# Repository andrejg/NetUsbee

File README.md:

# NetUsbee
A redraw of the famous network and usb adapter for 16/32bit Atari computers based on RTL8019AS and ISP1160

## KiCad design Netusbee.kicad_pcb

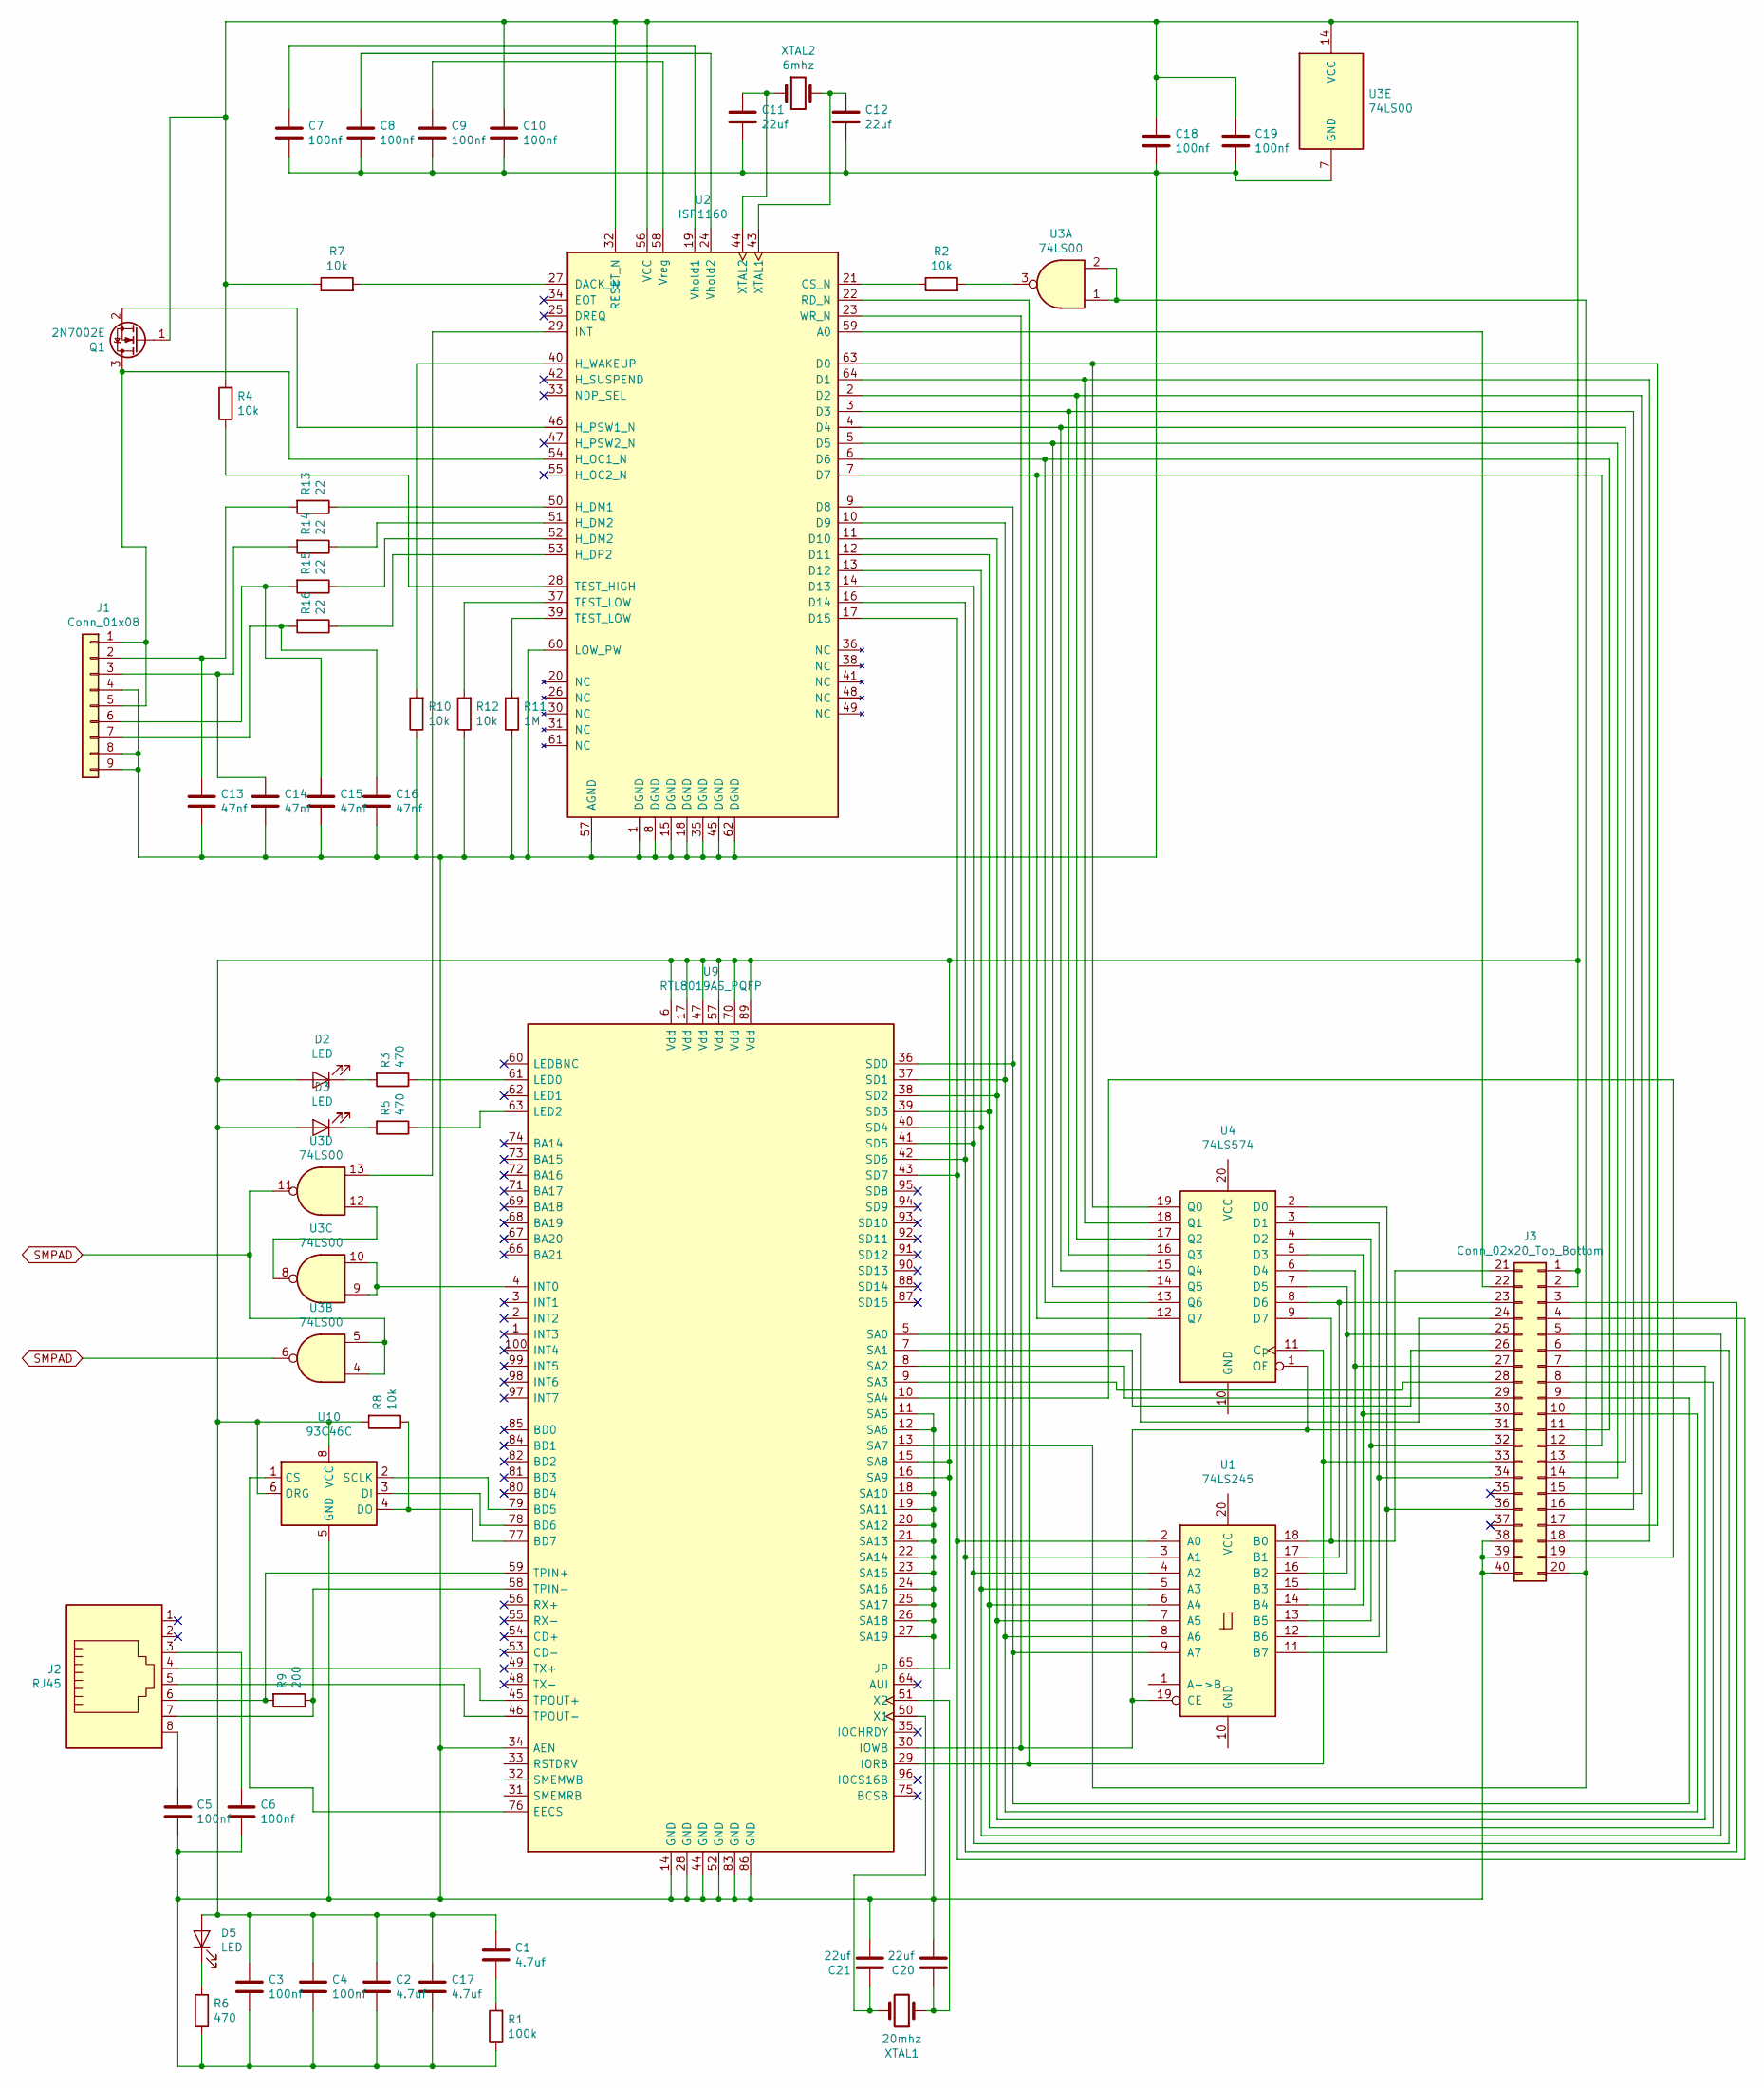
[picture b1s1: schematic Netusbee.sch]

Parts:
C1, C2, C17: 4.7uf; C_0805_2012Metric_Pad1.15x1.40mm_HandSolder
C3, C4, C5, C6, C7, C8, C9, C10, C18, C19: 100nf; C_0603_1608Metric_Pad1.05x0.95mm_HandSolder
C11, C12, C20, C21: 22uf; C_0603_1608Metric_Pad1.05x0.95mm_HandSolder
C13, C14, C15, C16: 47nf; C_0603_1608Metric_Pad1.05x0.95mm_HandSolder
D2, D3, D5: LED
J1: Conn_01x08; USB_A_Wuerth_61400826021_Horizontal_Stacked
J2: RJ45; RJ45_Amphenol_54602-x08_Horizontal
J3: Conn_02x20_Top_Bottom; AtariCartConnector
Q1: 2N7002E; SOT-23
R1: 100k; R_0603_1608Metric_Pad1.05x0.95mm_HandSolder
R2, R4, R7, R8, R10, R12: 10k; R_0603_1608Metric_Pad1.05x0.95mm_HandSolder
R3, R5, R6: 470; R_0603_1608Metric_Pad1.05x0.95mm_HandSolder
R9: 200; R_0603_1608Metric_Pad1.05x0.95mm_HandSolder
R11: 1M; R_0603_1608Metric_Pad1.05x0.95mm_HandSolder
R13, R14, R15, R16: 22; R_0603_1608Metric_Pad1.05x0.95mm_HandSolder
U1: 74LS245; SO-20_12.8x7.5mm_P1.27mm
U2: ISP1160; TQFP-64_10x10mm_P0.5mm
U3: 74LS00; TSSOP-14_4.4x5mm_P0.65mm
U4: 74LS574; SO-20_12.8x7.5mm_P1.27mm
U9: RTL8019AS_PQFP; PQFP-100_14x20mm_P0.65mm
U10: 93C46C; SOIC-8_3.9x4.9mm_P1.27mm
XTAL1: 20mhz; Crystal_SMD_HC49-SD
XTAL2: 6mhz; Crystal_SMD_HC49-SD

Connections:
unnamed: C1.1, C2.1, C3.1, C4.1, C10.1, C17.1, C18.1, C19.1, D2.2 (A), D3.2 (A), D5.2 (A), J3.1, J3.2, Q1.1 (G), R4.2, R7.1, R8.2, U2.32 (RESET_N), U2.56 (VCC), U3.14 (VCC), U9.6 (Vdd), U9.15 (SA8), U9.16 (SA9), U9.17 (Vdd), U9.47 (Vdd), U9.57 (Vdd), U9.65 (JP), U9.70 (Vdd), U9.89 (Vdd), U10.6 (ORG), U10.8 (VCC)
unnamed: C1.2, R1.2
unnamed: C5.1, J2.8
unnamed: C6.1, J2.3
unnamed: C7.1, U2.19 (Vhold1)
unnamed: C8.1, U2.24 (Vhold2)
unnamed: C9.1, U2.58 (Vreg)
unnamed: C2.2, C3.2, C4.2, C5.2, C6.2, C7.2, C8.2, C9.2, C10.2, C11.2, C12.2, C13.2, C14.2, C15.2, C16.2, C17.2, C18.2, C19.2, C20.2, C21.2, J1.4, J1.8, J1.9, J3.38, J3.39, J3.40, R1.1, R6.1, R10.1, R11.1, R12.1, U2.1 (DGND), U2.8 (DGND), U2.15 (DGND), U2.18 (DGND), U2.35 (DGND), U2.45 (DGND), U2.57 (AGND), U2.60 (LOW_PW), U2.62 (DGND), U3.7 (GND), U9.11 (SA5), U9.12 (SA6), U9.14 (GND), U9.18 (SA10), U9.19 (SA11), U9.20 (SA12), U9.21 (SA13), U9.22 (SA14), U9.23 (SA15), U9.24 (SA16), U9.25 (SA17), U9.26 (SA18), U9.27 (SA19), U9.28 (GND), U9.34 (AEN), U9.44 (GND), U9.52 (GND), U9.83 (GND), U9.86 (GND), U10.5 (GND)
unnamed: C11.1, U2.44 (XTAL2), XTAL2.1
unnamed: C12.1, U2.43 (XTAL1), XTAL2.2
unnamed: C13.1, J1.2, R13.2
unnamed: C14.1, J1.3, R14.2
unnamed: C15.1, J1.6, R15.2
unnamed: C16.1, J1.7, R16.2
unnamed: C20.1, U9.51 (X2), XTAL1.1
unnamed: C21.1, U9.50 (X1), XTAL1.2
unnamed: D2.1 (K), R3.2
unnamed: D3.1 (K), R5.2
unnamed: D5.1 (K), R6.2
unnamed: J1.1, J1.5, Q1.3 (D), U2.54 (H_OC1_N)
unnamed: J2.4, U9.45 (TPOUT+)
unnamed: J2.5, U9.46 (TPOUT-)
unnamed: J2.6, R9.2, U9.59 (TPIN+)
unnamed: J2.7, R9.1, U9.58 (TPIN-)
unnamed: J3.3, U1.3 (A1), U2.16 (D14), U9.42 (SD6)
unnamed: J3.4, U1.2 (A0), U2.17 (D15), U9.43 (SD7)
unnamed: J3.5, U1.5 (A3), U2.13 (D12), U9.40 (SD4)
unnamed: J3.6, U1.4 (A2), U2.14 (D13), U9.41 (SD5)
unnamed: J3.7, U1.7 (A5), U2.11 (D10), U9.38 (SD2)
unnamed: J3.8, U1.6 (A4), U2.12 (D11), U9.39 (SD3)
unnamed: J3.9, U1.9 (A7), U2.9 (D8), U9.36 (SD0)
unnamed: J3.10, U1.8 (A6), U2.10 (D9), U9.37 (SD1)
unnamed: J3.11, U2.6 (D6), U4.13 (Q6)
unnamed: J3.12, U2.7 (D7), U4.12 (Q7)
unnamed: J3.13, U2.4 (D4), U4.15 (Q4)
unnamed: J3.14, U2.5 (D5), U4.14 (Q5)
unnamed: J3.15, U2.2 (D2), U4.17 (Q2)
unnamed: J3.16, U2.3 (D3), U4.16 (Q3)
unnamed: J3.17, U2.63 (D0), U4.19 (Q0)
unnamed: J3.18, U2.64 (D1), U4.18 (Q1)
unnamed: J3.19, U9.10 (SA4)
unnamed: J3.20, U3.1, U3.2, U9.13 (SA7)
unnamed: J3.21, U1.18 (B0), U4.9 (D7)
unnamed: J3.22, U2.59 (A0)
unnamed: J3.23, U1.17 (B1), U4.8 (D6)
unnamed: J3.24, U9.5 (SA0)
unnamed: J3.25, U1.16 (B2), U4.7 (D5)
unnamed: J3.26, U9.7 (SA1)
unnamed: J3.27, U1.15 (B3), U4.6 (D4)
unnamed: J3.28, U9.9 (SA3)
unnamed: J3.29, U9.8 (SA2)
unnamed: J3.30, U1.14 (B4), U4.5 (D3)
unnamed: J3.31, U1.19 (CE), U2.23 (WR_N), U4.1 (OE), U9.30 (IOWB)
unnamed: J3.32, U1.13 (B5), U4.4 (D2)
unnamed: J3.33, U2.22 (RD_N), U4.11 (Cp), U9.29 (IORB)
unnamed: J3.34, U1.12 (B6), U4.3 (D1)
unnamed: J3.36, U1.11 (B7), U4.2 (D0)
unnamed: Q1.2 (S), U2.46 (H_PSW1_N)
unnamed: R2.1, U2.21 (CS_N)
unnamed: R2.2, U3.3
unnamed: R3.1, U9.61 (LED0)
unnamed: R4.1, U2.28 (TEST_HIGH)
unnamed: R5.1, U9.63 (LED2)
unnamed: R7.2, U2.27 (DACK_N)
unnamed: R8.1, U9.77 (BD7), U10.4 (DO)
unnamed: R10.2, U2.40 (H_WAKEUP)
unnamed: R11.2, U2.39 (TEST_LOW)
unnamed: R12.2, U2.37 (TEST_LOW)
unnamed: R13.1, U2.50 (H_DM1)
unnamed: R14.1, U2.51 (H_DM2)
unnamed: R15.1, U2.52 (H_DM2)
unnamed: R16.1, U2.53 (H_DP2)
unnamed: U2.29 (INT), U3.13
unnamed: U3.9, U3.10, U9.4 (INT0)
unnamed: U3.8, U3.12
unnamed: U9.76 (EECS), U10.1 (CS)
unnamed: U9.79 (BD5), U10.2 (SCLK)
unnamed: U9.78 (BD6), U10.3 (DI)
SMPAD: U3.4, U3.5, U3.6, U3.11

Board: 2 copper layers, 49 parts (4 on the bottom side), 76 nets, no tracks yet.

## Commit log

2021-05-12 Inital commit
